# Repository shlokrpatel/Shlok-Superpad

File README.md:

# Shlok-Superpad
A macropad I fully designed with help from hackclub with 9 keys in a matrix, a rotary encoder, oled screen, and rgb backlighing for each key.

# CAD
I'm screwing direcrly into the plastic with 2.9mm holes for construction of the case. The 2 parts are the top (with the mercedes logo) and the bottom.

# PCB

# Case

# BOM
1 Seeeduino XIAO RP2040

9 MX- style switches

9 DSA keycaps

10 1N4148 Diodes

1 EC11 rotary encoder

9 SK6812 MINI-E LEDs

1 0.91 in OLED 

1 custom pcb

1 3D printed case(2 parts)

4 M3x16mm scews

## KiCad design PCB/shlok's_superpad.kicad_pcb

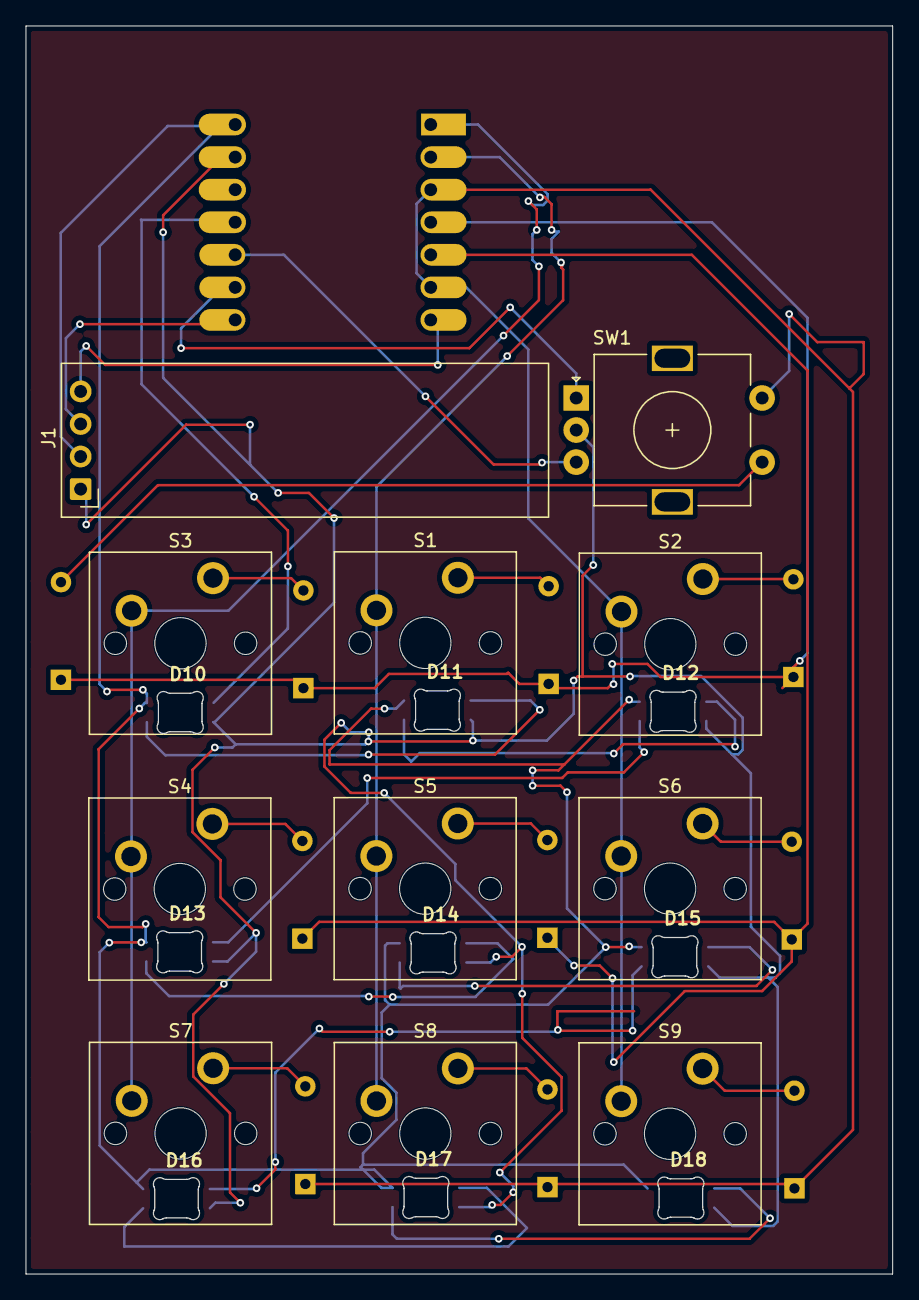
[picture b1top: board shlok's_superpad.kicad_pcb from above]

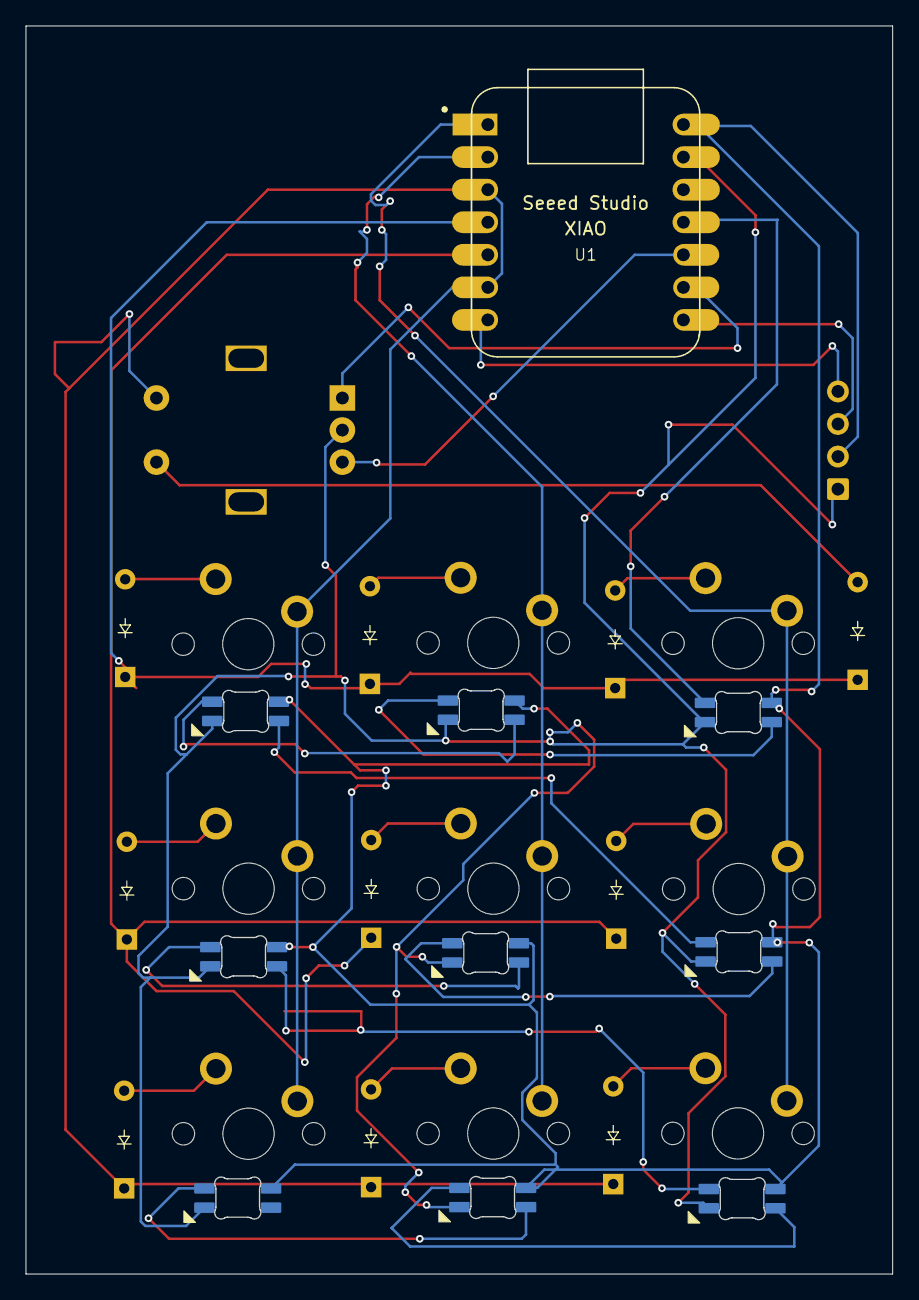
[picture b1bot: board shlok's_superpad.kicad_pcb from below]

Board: 2 copper layers, 67.6 x 97.3 mm, 31 parts (11 on the bottom side), 30 nets.

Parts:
D1, D2, D3, D4, D5, D6, D7, D8, D9, D19: Diode_DO-35
D10, D11, D12, D13, D14, D15, D16, D17, D18: SK6812MINI-E; SK6812MINI-E_fixed
J1: OLED_DISPLAY; ER_OLEDM0.91_1x-I2C
S1, S2, S3, S4, S5, S6, S7, S8, S9: MX_PCB_1.00u
SW1: RotaryEncoder_Switch; RotaryEncoder_Alps_EC11E-Switch_Vertical_H20mm
U1: MOUDLE-SEEEDUINO-XIAO; XIAO-Generic-Hybrid-14P-2.54-21X17.8MM

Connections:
+5V: D10.1 (VDD), D11.1 (VDD), D12.1 (VDD), D13.1 (VDD), D14.1 (VDD), D15.1 (VDD), D16.1 (VDD), D17.1 (VDD), D18.1 (VDD), J1.2, U1.14 (5V)
COLUMN 0: S3.1, S4.1, S7.1, U1.1 (PA02_A0_D0)
COLUMN 1: S1.1, S5.1, S8.1, U1.2 (PA4_A1_D1)
COLUMN 2: D7.1 (K), D8.1 (K), D9.1 (K), S2.1, S6.1, S9.1, SW1.S2, U1.3 (PA10_A2_D2), U1.6 (PA9_A5_D5_SCL)
GND: D10.3 (VSS), D11.3 (VSS), D12.3 (VSS), D13.3 (VSS), D14.3 (VSS), D15.3 (VSS), D16.3 (VSS), D17.3 (VSS), D18.3 (VSS), J1.1, SW1.C, U1.13 (GND)
LED: D10.4 (DIN), U1.11 (PA6_A10_D10_MOSI)
unnamed: D1.2 (A), S1.2
unnamed: D2.2 (A), S2.2
unnamed: D3.2 (A), S3.2
unnamed: D4.2 (A), S4.2
unnamed: D5.2 (A), S5.2
unnamed: D6.2 (A), S6.2
unnamed: D7.2 (A), S7.2
unnamed: D8.2 (A), S8.2
unnamed: D9.2 (A), S9.2
unnamed: D10.2 (DOUT), D11.4 (DIN)
unnamed: D11.2 (DOUT), D12.4 (DIN)
unnamed: D12.2 (DOUT), D13.4 (DIN)
unnamed: D13.2 (DOUT), D14.4 (DIN)
unnamed: D14.2 (DOUT), D15.4 (DIN)
unnamed: D15.2 (DOUT), D16.4 (DIN)
unnamed: D16.2 (DOUT), D17.4 (DIN)
unnamed: D17.2 (DOUT), D18.4 (DIN)
unnamed: J1.3, U1.8 (PB09_A7_D7_RX)
unnamed: J1.4, U1.7 (PB08_A6_D6_TX)
unnamed: SW1.B, U1.10 (PA5_A9_D9_MISO)
unnamed: SW1.A, U1.9 (PA7_A8_D8_SCK)
RES 1: D19.2 (A), SW1.S1
ROW 0: D1.1 (K), D2.1 (K), D3.1 (K), D19.1 (K), U1.4 (PA11_A3_D3)
ROW 1: D4.1 (K), D5.1 (K), D6.1 (K), U1.5 (PA8_A4_D4_SDA)
